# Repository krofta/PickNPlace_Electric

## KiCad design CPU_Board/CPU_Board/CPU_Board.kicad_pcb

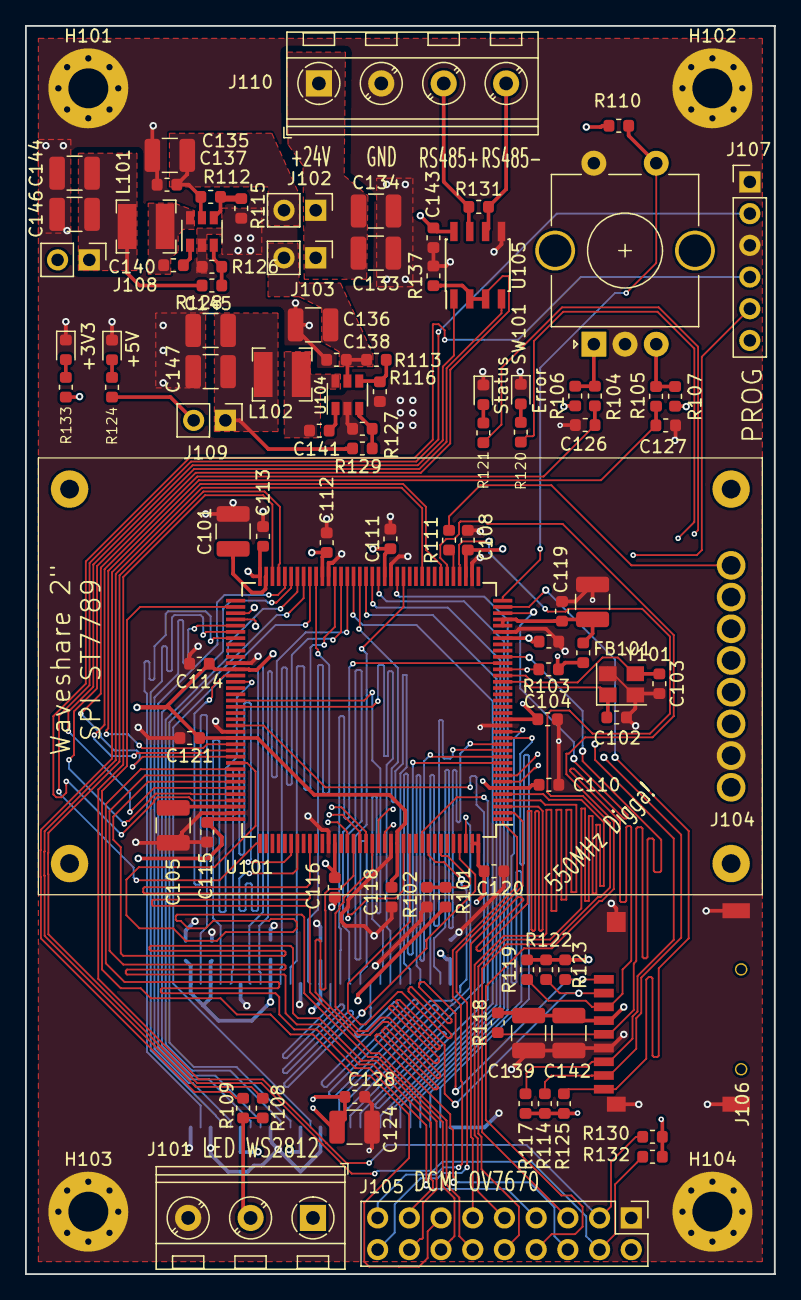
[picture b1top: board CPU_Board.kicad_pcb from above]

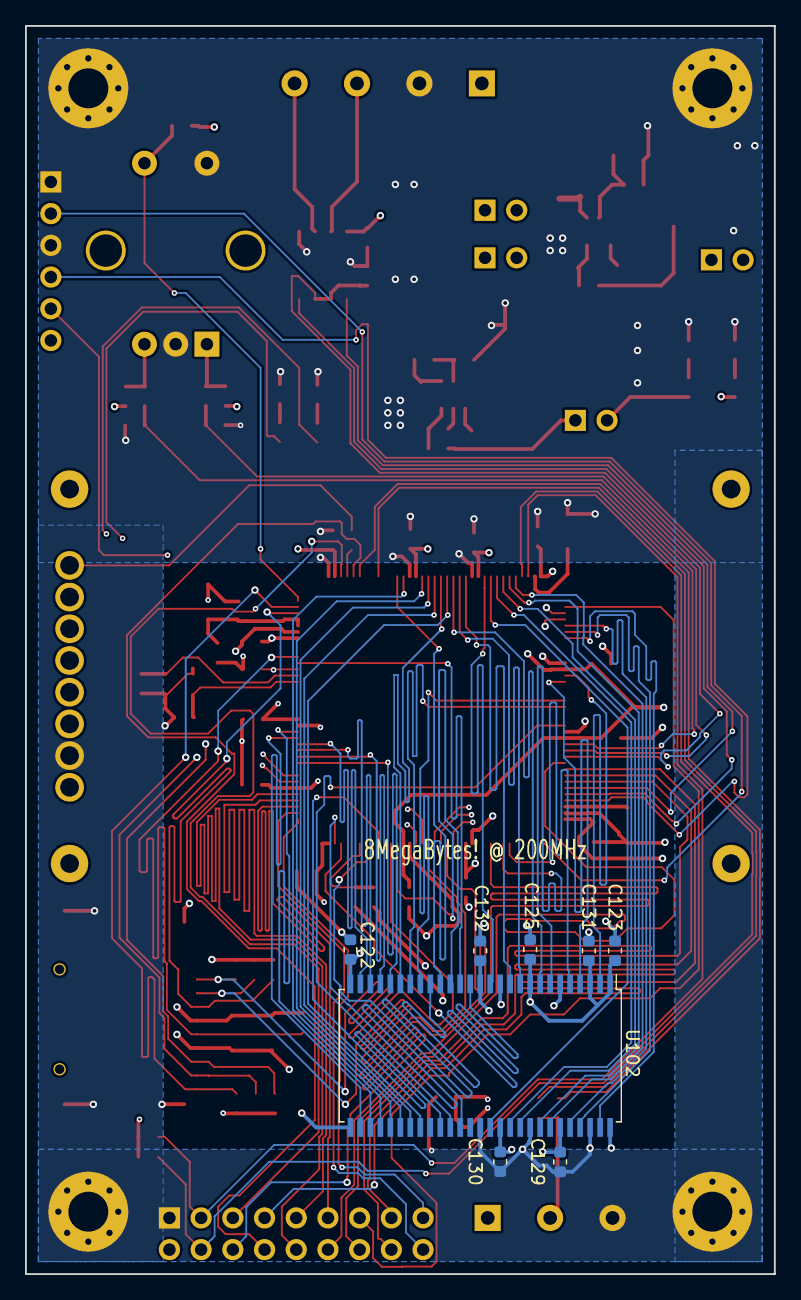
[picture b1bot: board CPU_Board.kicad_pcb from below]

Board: 4 copper layers, 60.0 x 100.0 mm, 107 parts (8 on the bottom side), 112 nets.

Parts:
C101, C105: 2.2u; C_1210_3225Metric
C102, C103: 18p; C_0603_1608Metric
C104, C106, C108, C110, C111, C112, C113, C114, C115, C116, C118, C119, C120, C121, C122, C123, C125, C126, C127, C128, C129, C130, C131, C132, C137, C138, C140, C141, C143: 100n; C_0603_1608Metric
C117, C124, C133, C134, C135, C136, C139, C142, C144, C145, C146, C147: 10u; C_1210_3225Metric
D101, D103, D104: LED_blue; LED_0603_1608Metric
D102: LED_red; LED_0603_1608Metric
FB101: 70R; L_0603_1608Metric
H101, H102, H103, H104: MountingHole_Pad; MountingHole_3.2mm_M3_Pad_Via
J101: Screw_Terminal_01x03; TerminalBlock_RND_205-00046_1x03_P5.00mm_Horizontal
J102, J103, J108, J109: Conn_02x01; PinHeader_1x02_P2.54mm_Vertical
J104: Conn_01x08_Male; ST7789_Waveshare
J105: Conn_02x09_Odd_Even; PinHeader_2x09_P2.54mm_Vertical
J106: Micro_SD_Card_Det; TF-115-BCP9
J107: Conn_01x06_Male; PinHeader_1x06_P2.54mm_Vertical
J110: Screw_Terminal_01x04; TerminalBlock_RND_205-00047_1x04_P5.00mm_Horizontal
L101, L102: 12u SRN4018; L_Bourns-SRN4018
R101: DNP; R_0603_1608Metric
R102, R103, R104, R105, R125, R137: 10K; R_0603_1608Metric
R106, R107, R108, R109, R110, R111, R120, R121, R124, R130, R132, R133: 1K; R_0603_1608Metric
R112, R113, R115, R116, R128: 51K; R_0603_1608Metric
R114, R117, R118, R119, R122, R123, R126, R127: 22K1; R_0603_1608Metric
R129: 88K7; R_0603_1608Metric
R131: 100R; R_0603_1608Metric
SW101: Rotary_Encoder_Switch; RotaryEncoder_Alps_EC11E-Switch_Vertical_H20mm_CircularMoun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
U101: STM32H730ZB; LQFP-144_20x20mm_P0.5mm
U102: W9864G6KH; TSOP-II-54_22.2x10.16mm_P0.8mm
U103, U104: TPS560430; SOT-23-6
U105: ST3485ECDR; SOIC-8_3.9x4.9mm_P1.27mm
Y101: 48MHz; Crystal_SMD_3225-4Pin_3.2x2.5mm

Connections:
+3V3: C104.1, C106.1, C108.1, C110.1, C111.1, C112.1, C113.1, C114.1, C115.1, C116.1, C118.1, C120.1, C121.1, C122.1, C123.1, C125.1, C129.1, C130.1, C131.1, C132.1, C139.1, C142.1, C143.1, FB101.2, J104.1, J105.2, J106.4, J108.2, R101.2, R103.2, R106.1, R107.1, R110.1, R114.2, R117.2, R118.2, R119.2, R122.2, R123.2, R125.1, R130.1, R132.1, R133.1, U101.6, U101.17, U101.30, U101.39, U101.52, U101.62, U101.72, U101.84, U101.95, U101.108, U101.121, U101.131, U101.143, U101.144, U102.1, U102.3, U102.9, U102.14, U102.27, U102.43, U102.49, U105.8
+5V: C124.1, C128.1, J101.1, J109.2, R124.1
+24V: C133.1, C134.1, J102.1, J103.1, J110.1
/A0: U101.10, U102.23
/A1: U101.11, U102.24
/A2: U101.12, U102.25
/A3: U101.13, U102.26
/A4: U101.14, U102.29
/A5: U101.15, U102.30
/A6: U101.50, U102.31
/A7: U101.53, U102.32
/A8: U101.54, U102.33
/A9: U101.55, U102.34
/A10: U101.56, U102.22
/A11: U101.57, U102.35
/BA0: U101.89, U102.20
/BA1: U101.90, U102.21
/CAM_D0: J105.15, U101.101
/CAM_D1: J105.16, U101.102
/CAM_D2: J105.13, U101.74
/CAM_D3: J105.14, U101.99
/CAM_D4: J105.11, U101.3
/CAM_D5: J105.12, U101.117
/CAM_D6: J105.9, U101.4
/CAM_D7: J105.10, U101.5
/CAM_HSYNC: J105.5, U101.40
/CAM_PCLK: J105.8, U101.42
/CAM_PWDN: J105.17, U101.1
/CAM_RESET: J105.18, U101.2
/CAM_SIOC: J105.4, R132.2, U101.69
/CAM_SIOD: J105.3, R130.2, U101.70
/CAM_VSYNC: J105.6, U101.124
/CAM_XCLK: J105.7, U101.100
/DISP_BL: J104.8, R111.2
/DISP_CD: J104.5, U101.129
/DISP_CLK: J104.4, U101.126
/DISP_DC: J104.6, U101.128
/DISP_DIN: J104.3, U101.123
/DISP_RST: J104.7, U101.125
/DQ0: U101.85, U102.2
/DQ1: U101.86, U102.4
/DQ2: U101.114, U102.5
/DQ3: U101.115, U102.7
/DQ4: U101.58, U102.8
/DQ5: U101.59, U102.10
/DQ6: U101.60, U102.11
/DQ7: U101.63, U102.13
/DQ8: U101.64, U102.42
/DQ9: U101.65, U102.44
/DQ10: U101.66, U102.45
/DQ11: U101.67, U102.47
/DQ12: U101.68, U102.48
/DQ13: U101.77, U102.50
/DQ14: U101.78, U102.51
/DQ15: U101.79, U102.53
/NBL0: U101.141, U102.15
/NBL1: U101.142, U102.39
/NRST: J107.5, R103.1, U101.25
/PA0: J106.3, R119.1, U101.34
/PA1: J106.9, R125.2, U101.35
/PA2: R110.2, SW101.S1, U101.36
/PA5: R111.1, U101.41
/PA7: R109.1, U101.43
/PA11: U101.103, U105.1
/PA12: U101.104, U105.4
/PA13: J107.4, U101.105
/PA14: J107.2, U101.109
/PB0: R108.1, U101.46
/PB3: J106.1, R123.1, U101.133
/PB5: U101.135, U102.37
/PB6: U101.136, U102.19
/PB14: J106.7, R117.1, U101.75
/PB15: J106.8, R114.1, U101.76
/PC0: U101.26, U102.16
/PC1: J106.5, R118.1, U101.27
/PC6: C127.1, R105.2, U101.96
/PC7: C126.2, R104.2, U101.97
/PC8: R137.1, U101.98, U105.2, U105.3
/PC13: R120.1, U101.7
/PC14: R121.1, U101.8
/PF11: U101.49, U102.18
/PG8: U101.93, U102.38
/PG12: J106.2, R122.1, U101.127
/PG15: U101.132, U102.17
/PH0: C102.1, U101.23, Y101.1
/PH1: C103.1, U101.24, Y101.3
/RS485+: J110.3, R131.1, U105.7
/RS485-: J110.4, R131.2, U105.6
/VREF: C117.1, C119.1, FB101.1, U101.32, U101.33
GND: C101.2, C102.2, C103.2, C104.2, C105.2, C106.2, C108.2, C110.2, C111.2, C112.2, C113.2, C114.2, C115.2, C116.2, C117.2, C118.2, C119.2, C120.2, C121.2, C122.2, C123.2, C124.2, C125.2, C126.1, C127.2, C128.2, C129.2, C130.2, C131.2, C132.2, C133.2, C134.2, C135.2, C136.2, C137.2, C138.2, C139.2, C142.2, C143.2, C144.2, C145.2, C146.2, C147.2, D101.1, D102.1, D103.1, D104.1, H101.1, H102.1, H103.1, H104.1, J101.3, J104.2, J105.1, J106.6, J106.10, J107.1, J107.3, J110.2, R102.2, R115.1, R116.1, R126.1, R127.1, R137.2, SW101.C, SW101.S2, U101.16, U101.31, U101.38, U101.51, U101.61, U101.83, U101.94, U101.107, U101.120, U101.130, U102.6, U102.12, U102.28, U102.41, U102.46, U102.52, U102.54, U103.2, U104.2, U105.5, Y101.2, Y101.4
unnamed: C101.1, U101.71
unnamed: C105.1, U101.106
unnamed: C135.1, C137.1, J102.2, R112.1, U103.5
unnamed: C136.1, C138.1, J103.2, R113.1, U104.5
unnamed: C140.1, L101.1, U103.6
unnamed: C140.2, U103.1
unnamed: C141.1, L102.1, U104.6
unnamed: C141.2, U104.1
unnamed: C144.1, C146.1, J108.1, L101.2, R128.2
unnamed: C145.1, C147.1, J109.1, L102.2, R129.2
unnamed: D101.2, R120.2
unnamed: D102.2, R121.2
unnamed: D103.2, R124.2
unnamed: D104.2, R133.2
unnamed: J101.2, R108.2, R109.2
unnamed: R101.1, R102.1, U101.138
unnamed: R104.1, R106.2, SW101.A
unnamed: R105.1, R107.2, SW101.B
unnamed: R112.2, R115.2, U103.4
unnamed: R113.2, R116.2, U104.4
unnamed: R126.2, R128.1, U103.3
unnamed: R127.2, R129.1, U104.3
